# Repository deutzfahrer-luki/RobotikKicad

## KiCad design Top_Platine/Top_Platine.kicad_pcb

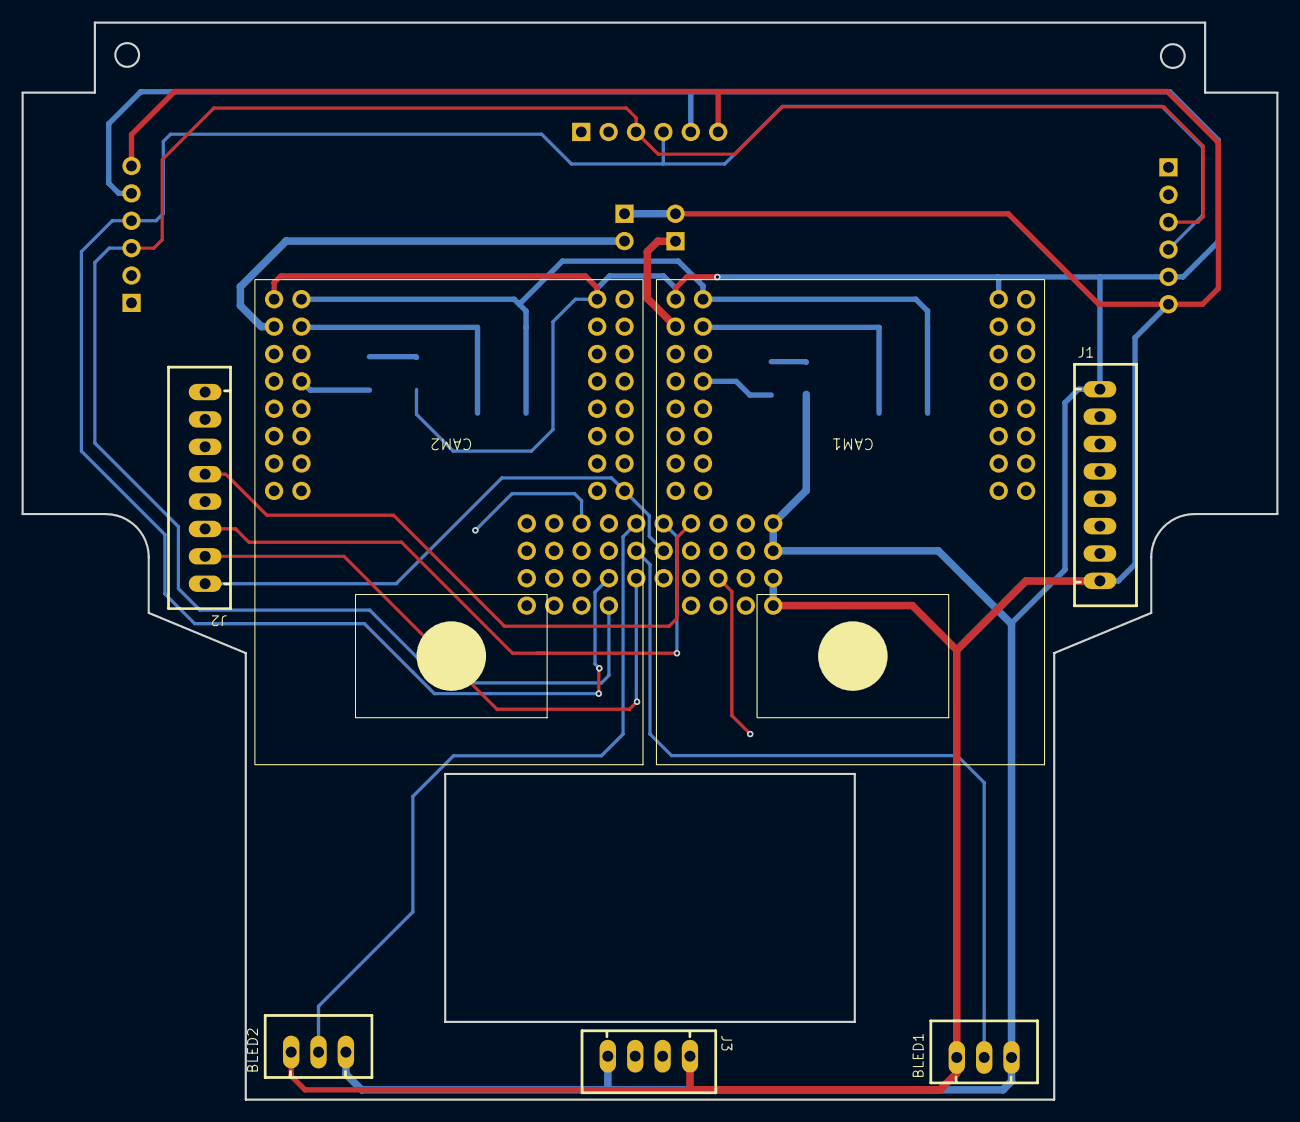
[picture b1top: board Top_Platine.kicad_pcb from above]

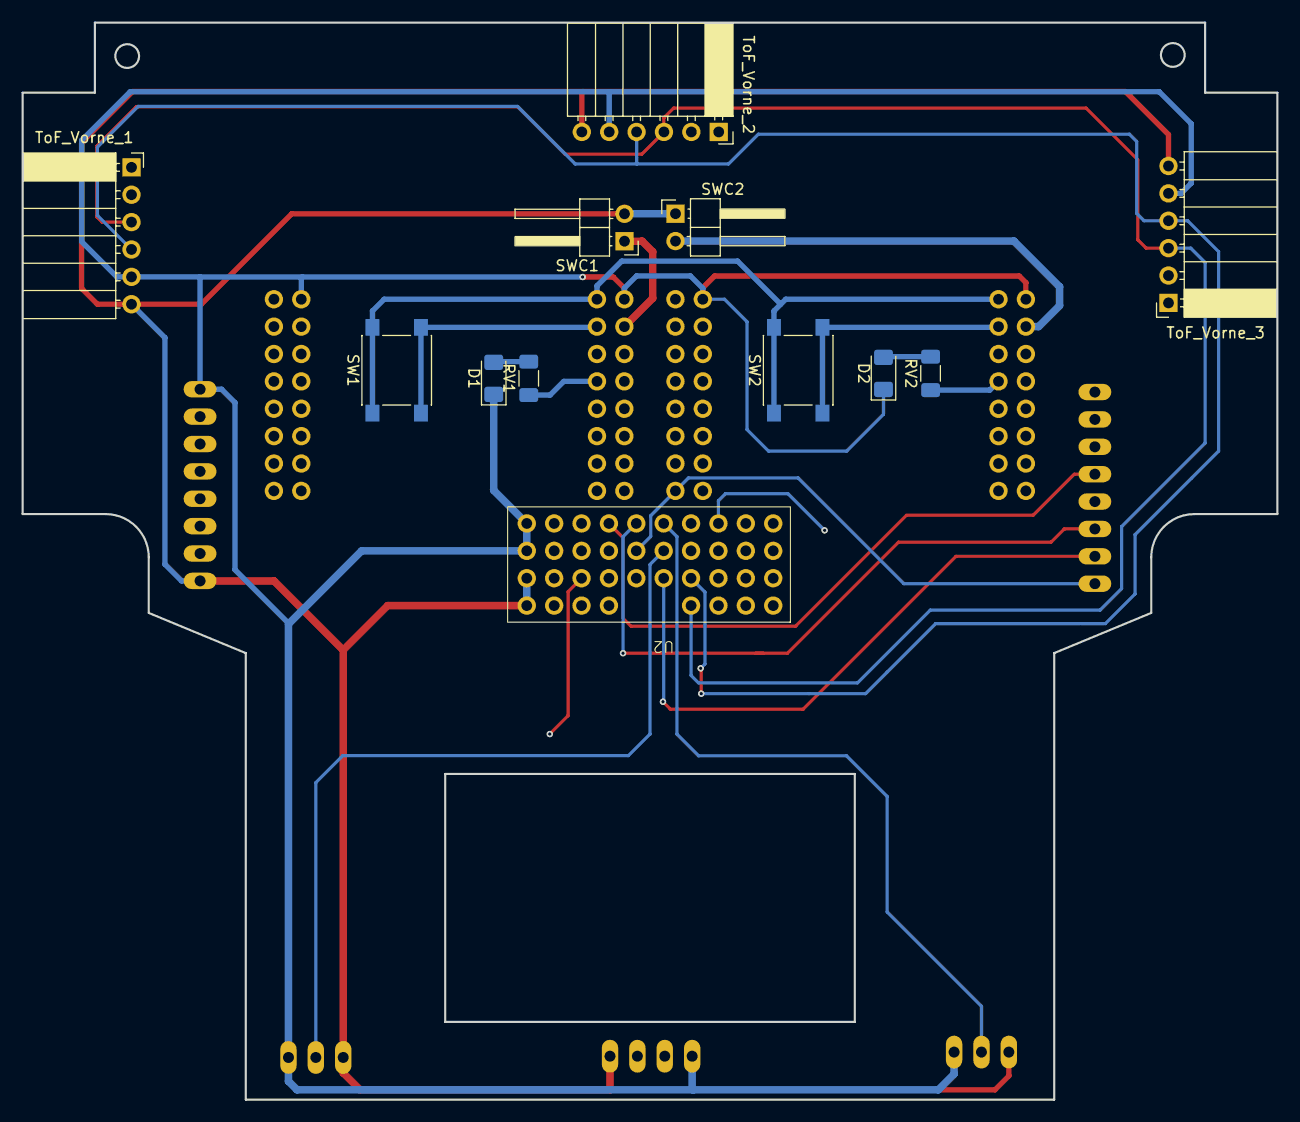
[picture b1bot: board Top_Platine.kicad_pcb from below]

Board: 4 copper layers, 116.4 x 99.9 mm, 19 parts (12 on the bottom side), 42 nets.

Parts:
BLED1, BLED2: Conn_01x03_Pin; JST-XH-03-PACKAGE-LONG-PAD
CAM1, CAM2: OpenMV_RT1062
D1, D2: LED; LED_1206_3216Metric_Pad1.42x1.75mm_HandSolder
J1, J2: Conn_01x08_Pin; JST-XH-08-PACKAGE-LONG-PAD
J3: Conn_01x04_Pin; JST-XH-04-PACKAGE-LONG-PAD
RV1, RV2: 220; R_1206_3216Metric_Pad1.30x1.75mm_HandSolder
SW1, SW2: SW_SPST; SW_SPST_PTS645
SWC1, SWC2: SW_SPST; PinHeader_1x02_P2.54mm_Horizontal
ToF_Vorne_1, ToF_Vorne_2, ToF_Vorne_3: Conn_01x06_Socket; PinSocket_1x06_P2.54mm_Horizontal
U2: Main Conector to Main pcb; Main Conetor

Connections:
+3.3V: CAM1.17 (3.3V), CAM2.17 (3.3V), SW1.1 (A), SW2.1 (A)
+5V: BLED1.1, BLED2.1, J1.8, J3.1, SWC1.2 (B), SWC2.1 (A), ToF_Vorne_1.6, ToF_Vorne_2.6, ToF_Vorne_3.6, U2.5V
/BLED_C1: BLED1.2, U2.LED1 (Beleuchtung_Cam_1)
/BLED_C2: BLED2.2, U2.LED2 (Beleuchtung_Cam_2)
/BUTTON_1: J1.4, U2.UI_B1 (UI_Button_1)
/BUTTON_2: J1.5, U2.UI_B2 (UI_Button_2)
/BUTTON_3: J1.6, U2.UI_B3 (UI_Button_3)
/BUTTON_4: J1.7, U2.UI_B4 (UI_Button_4)
/CS_D: J2.5, U2.CS_D (CS_Display)
/D_D: J2.3, U2.D_D (D_Display)
/INTT_C1: CAM1.29 (P9), U2.R_C1 (Reset_Cam_1)
/INTT_C2: CAM2.29 (P9), U2.R_C2 (Reset_Cam_2)
/INT_C1: CAM1.30 (P10), U2.I_C1 (Interrupt_Cam_1)
/INT_C2: CAM2.30 (P10), U2.I_C2 (Interrupt_Cam_2)
/Kamera/Kamera1/5V: CAM1.26 (VIN), SWC1.1 (A)
/Kamera/Kamera1/State_LED: CAM1.20 (P14), RV1.1
/Kamera/Kamera2/5V: CAM2.26 (VIN), SWC2.2 (B)
/Kamera/Kamera2/State_LED: CAM2.20 (P14), RV2.1
/LED_A: J1.2, U2.LED_A (UI_Led_1)
/LED_B: J1.3, U2.LED_B (UI_Led_2)
/MOSI: J2.1, U2.MOSI
/RES: J2.4, U2.1 (RES_D)
/RE_A: J2.6, U2.RE_A (Encoder_A)
/RE_B: J2.8, U2.RE_B (Encoder_B)
/RE_SW: J2.7, U2.RE_SW (Encoder_Taster)
/RX_C1: CAM1.3 (P5/U_RX/SDA), U2.RX_C1 (RX_Cam_1)
/RX_C2: CAM2.3 (P5/U_RX/SDA), U2.RX_C2 (RX_Cam_2)
/SCK: J2.2, U2.SCK
/SCL: ToF_Vorne_1.3, ToF_Vorne_2.3, ToF_Vorne_3.3, U2.SDA
/SDA: ToF_Vorne_1.4, ToF_Vorne_2.4, ToF_Vorne_3.4, U2.SCL
/TX_C1: CAM1.4 (P4/U_TX/SCL), U2.TX_C1 (TX_Cam_1)
/TX_C2: CAM2.4 (P4/U_TX/SCL), U2.TX_C2 (TX_Cam_2)
/ToF_XS_1: ToF_Vorne_1.1, U2.TXS1 (ToF_XS_1)
/ToF_XS_2: ToF_Vorne_2.1, U2.TXS2 (ToF_XS_2)
/ToF_XS_3: ToF_Vorne_3.1, U2.TXS3 (ToF_XS_3)
GND: BLED1.3, BLED2.3, CAM1.9 (GND), CAM1.25 (GND), CAM2.9 (GND), CAM2.25 (GND), D1.1 (K), D2.1 (K), J1.1, J3.4, ToF_Vorne_1.5, ToF_Vorne_2.5, ToF_Vorne_3.5, U2.GND
unnamed: CAM1.18 (SBL), SW1.2 (B)
unnamed: CAM2.18 (SBL), SW2.2 (B)
unnamed: D1.2 (A), RV1.2
unnamed: D2.2 (A), RV2.2
unnamed: J3.2, U2.D+ (Mega_D+)
unnamed: J3.3, U2.D- (Mega_D-)

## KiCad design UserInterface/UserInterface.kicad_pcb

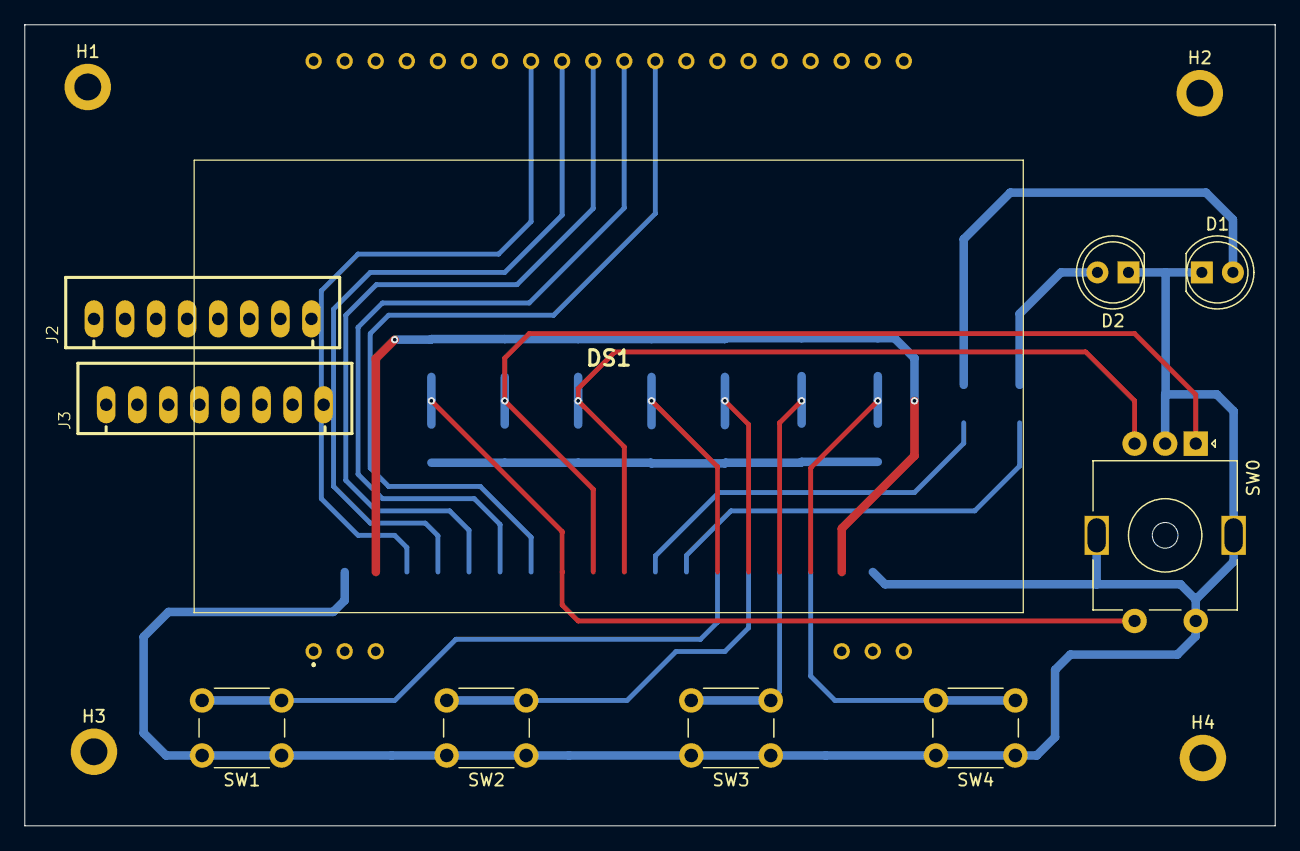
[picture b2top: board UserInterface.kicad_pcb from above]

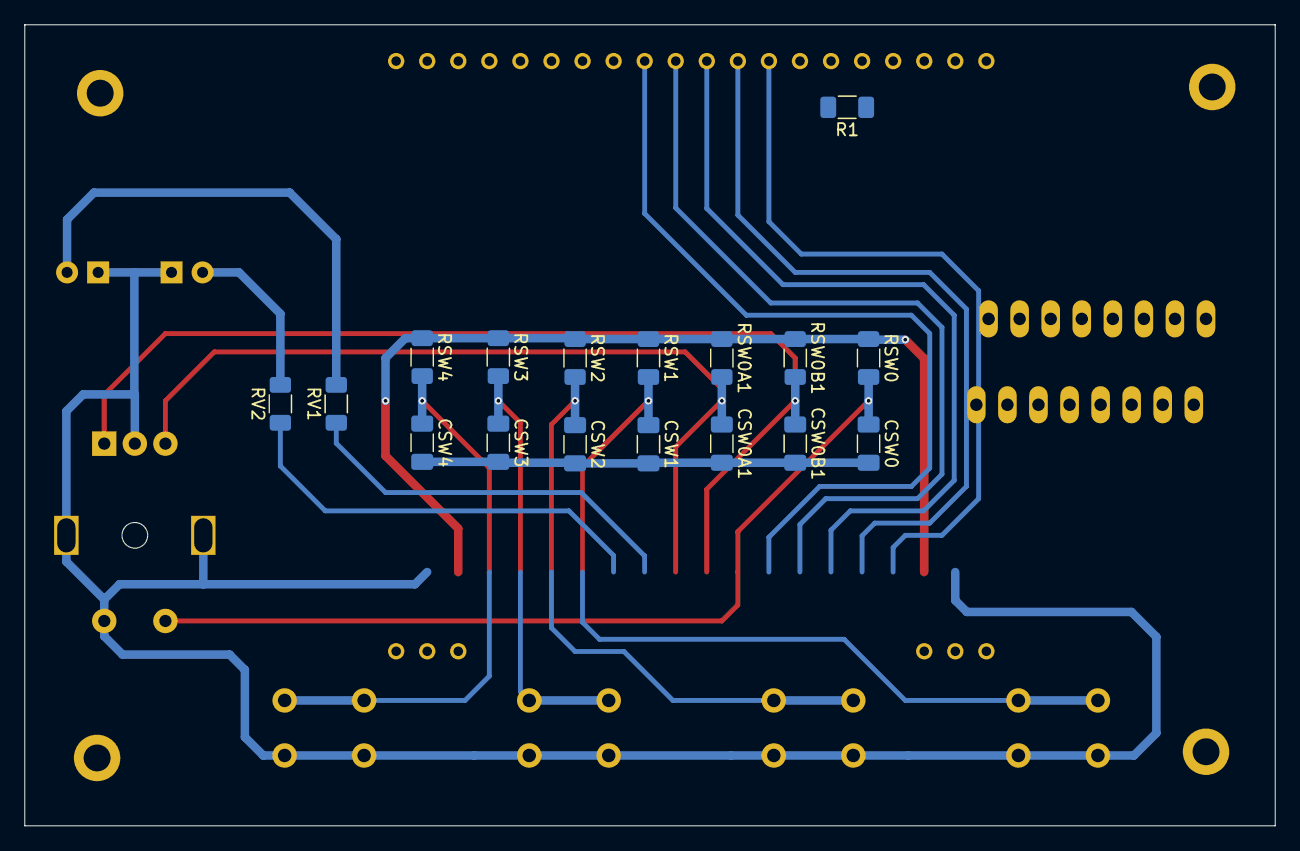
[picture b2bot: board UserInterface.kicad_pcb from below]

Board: 2 copper layers, 102.2 x 65.5 mm, 31 parts (17 on the bottom side), 18 nets.

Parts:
CSW0, CSW0A1, CSW0B1, CSW1, CSW2, CSW3, CSW4: 100n; C_1206_3216Metric_Pad1.33x1.80mm_HandSolder
D1, D2: LED; LED_D5.0mm
DS1: EA_OLEDL128-6GGA; EA OLEDL128-6GGA
H1, H2, H3, H4: MountingHole_Pad; MountingHole_2.2mm_M2_DIN965_Pad
J2, J3: Conn_01x08_Pin; JST-XH-08-PACKAGE-LONG-PAD
R1: 910K; R_1206_3216Metric_Pad1.30x1.75mm_HandSolder
RSW0, RSW0A1, RSW0B1, RSW1, RSW2, RSW3, RSW4: 10k; R_1206_3216Metric_Pad1.30x1.75mm_HandSolder
RV1, RV2: 220R; R_1206_3216Metric_Pad1.30x1.75mm_HandSolder
SW0: RotaryEncoder_Switch_MP; RotaryEncoder_Alps_EC11E-Switch_Vertical_H20mm_MountingHoles
SW1, SW2, SW3, SW4: SW_SPST; SW_PUSH_6mm_H7.3mm

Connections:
+5V: DS1.21 (VCC_1), DS1.22 (VCC_2), DS1.25 (VDD), DS1.39 (VCC_3), DS1.40 (VCC_4), J2.8, RSW0.1, RSW0A1.1, RSW0B1.1, RSW1.1, RSW2.1, RSW3.1, RSW4.1
/BUTTON_1: CSW1.1, J2.4, RSW1.2, SW1.2 (B)
/BUTTON_2: CSW2.1, J2.5, RSW2.2, SW2.2 (B)
/BUTTON_3: CSW3.1, J2.6, RSW3.2, SW3.2 (B)
/BUTTON_4: CSW4.1, J2.7, RSW4.2, SW4.2 (B)
/Display/IREF: DS1.36 (IREF), R1.1
/Display/VCOMH: DS1.37 (VCOMH_1), DS1.38 (VCOMH_2)
/LED_A: J2.2, RV1.1
/LED_B: J2.3, RV2.1
/MOSI: DS1.33 (D1), J3.1
/RES: DS1.30 (RES), J3.4
/RE_A: CSW0B1.1, J3.6, RSW0B1.2, SW0.A
/RE_B: CSW0A1.1, J3.8, RSW0A1.2, SW0.B
/RE_SW: CSW0.1, J3.7, RSW0.2, SW0.S1
/SCK: DS1.32 (D0), J3.2
GND: CSW0.2, CSW0A1.2, CSW0B1.2, CSW1.2, CSW2.2, CSW3.2, CSW4.2, D1.1 (K), D2.1 (K), DS1.23 (GND_1), DS1.24 (GND_2), DS1.26 (BS0), DS1.27 (BS1), DS1.28 (GND_3), DS1.35 (GND_4), H1.1, H2.1, H3.1, H4.1, J2.1, R1.2, SW0.C, SW0.MP, SW0.S2, SW1.1 (A), SW2.1 (A), SW3.1 (A), SW4.1 (A)
unnamed: D1.2 (A), RV1.2
unnamed: D2.2 (A), RV2.2

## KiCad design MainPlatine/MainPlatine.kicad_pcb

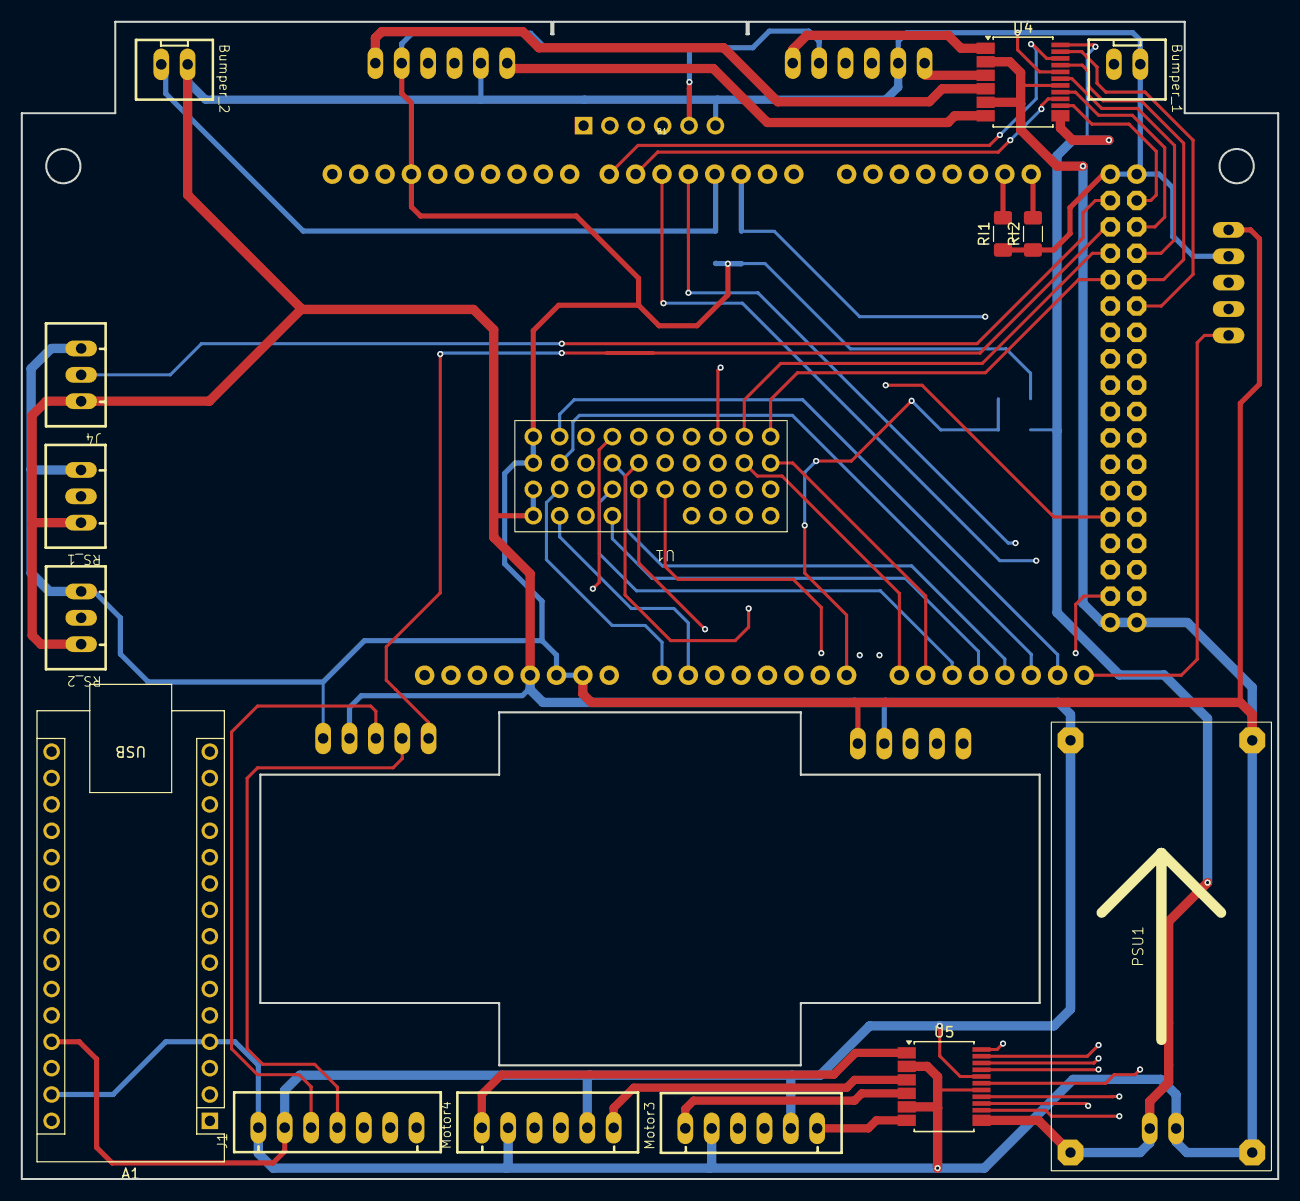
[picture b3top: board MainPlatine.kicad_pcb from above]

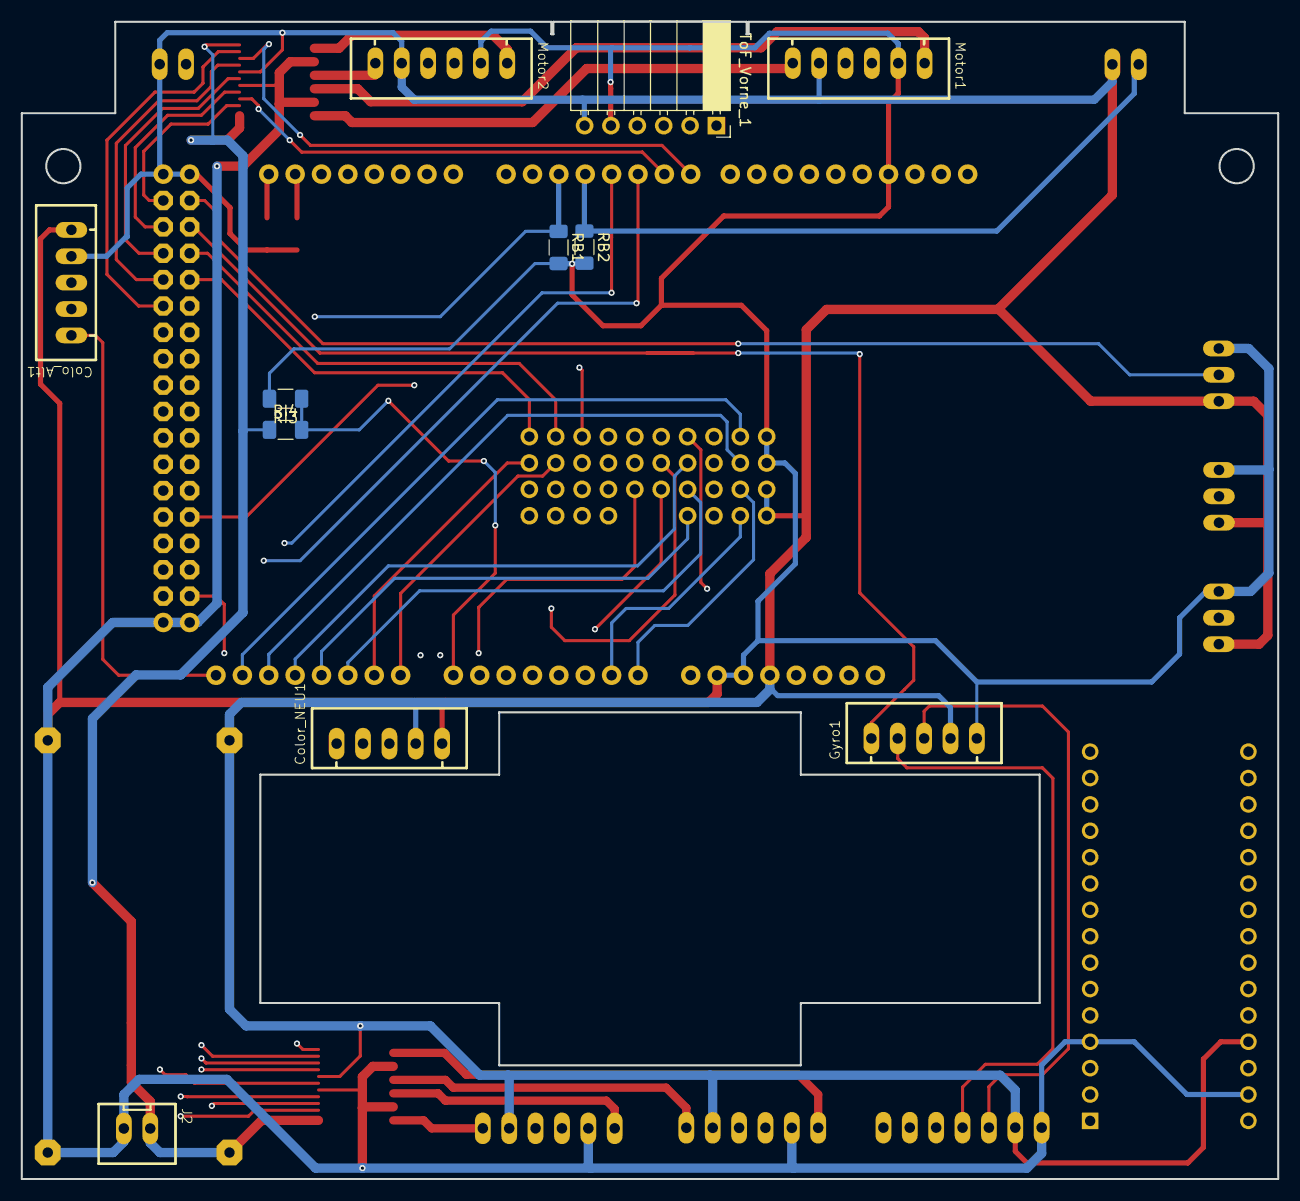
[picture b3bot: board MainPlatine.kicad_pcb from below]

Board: 4 copper layers, 121.0 x 111.5 mm, 27 parts (11 on the bottom side), 74 nets.

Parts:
A1: Arduino_Nano_v2.x; Arduino_Nano
B1: ARDUINO_MEGA_NO_SILK
Bumper_1, Bumper_2: Conn_01x02_Pin; JST-XH-02-PACKAGE-LONG-PAD
Colo_Alt1: Conn_01x05_Pin; JST-XH-05-PACKAGE-LONG-PAD
Color_NEU1: Conn_01x05_Pin; JST-XH-05-PACKAGE-LONG-PAD
Gyro1: Conn_01x05_Pin; JST-XH-05-PACKAGE-LONG-PAD
J1: Conn_01x07_Pin; JST-XH-07-PACKAGE-LONG-PAD
J2: Conn_01x02_Pin; JST-XH-02-PACKAGE-LONG-PAD
J4: Conn_01x03_Pin; JST-XH-03-PACKAGE-LONG-PAD
Motor1, Motor2, Motor3, Motor4: Conn_01x06_Pin; JST-XH-06-PACKAGE-LONG-PAD
PSU1: Untitled_1
RB1, RB2: 10k; R_1206_3216Metric_Pad1.30x1.75mm_HandSolder
RI1, RI2, RI3, RI4: 10k; R_1206_3216Metric_Pad1.30x1.75mm_HandSolder
RS_1, RS_2: Conn_01x03_Pin; JST-XH-03-PACKAGE-LONG-PAD
ToF_Vorne_1: Conn_01x06_Socket; PinSocket_1x06_P2.54mm_Horizontal
U1: Main Conector to Main pcb; Main Conetor
U4, U5: TB6612FNG; SSOP-24_5.3x8.2mm_P0.65mm

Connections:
+5V: A1.27 (+5V), B1.5V, Bumper_1.1, Bumper_2.1, Colo_Alt1.4, Color_NEU1.4, Gyro1.4, J1.2, J4.1, Motor1.5, Motor2.5, Motor3.5, Motor4.5, PSU1.OUT+ (VOUT+), RI1.1, RI2.1, RS_1.1, RS_2.1, ToF_Vorne_1.6, U1.5V, U4.20 (VCC), U5.20 (VCC)
/6V: J2.1, PSU1.IN+ (VIN+), RI4.1, U4.14 (VM3), U4.24 (VM1), U5.14 (VM3), U5.24 (VM1)
/ARD_RX_2: B1.17 (17(RX2)), U1.TX_C2 (TX_Cam_2)
/ARD_RX_3: A1.2 (D0/RX), B1.14 (14(TX3))
/ARD_TX_2: B1.16 (16(TX2)), U1.RX_C2 (RX_Cam_2)
/ARD_TX_3: A1.1 (D1/TX), B1.15 (15(RX3))
/BAT_ADC: B1.A7, RI3.1, RI4.2
/Bumper_Links: B1.2, Bumper_1.2, RB1.1
/Bumper_Rechts: B1.3, Bumper_2.2, RB2.1
/CS_D: B1.53 (53/~CS), U1.CS_D (CS_Display)
/Color_NEW_IO: B1.48, Color_NEU1.1
/Color_Old_Interrupt: B1.A15, Colo_Alt1.1
/D_D: B1.46, U1.D_D (D_Display)
/ENC1_A: A1.12 (D9), Motor2.4
/ENC1_B: A1.11 (D8), Motor2.3
/ENC2_A: A1.10 (D7), Motor1.4
/ENC2_B: A1.9 (D6), Motor1.3
/ENC3_A: A1.6 (D3), Motor4.4
/ENC3_B: A1.5 (D2), Motor4.3
/ENC4_A: A1.8 (D5), Motor3.4
/ENC4_B: A1.7 (D4), Motor3.3
/Encoder_A: B1.A12, U1.RE_A (Encoder_A)
/Encoder_B: B1.A10, U1.RE_B (Encoder_B)
/Encoder_SW: B1.A11, U1.RE_SW (Encoder_Taster)
/GYRO_RST: B1.24, Gyro1.1
/IO_CAM2: B1.26, U1.R_C2 (Reset_Cam_2)
/Interrupt_Cam1: B1.A8, U1.I_C2 (Interrupt_Cam_2)
/LEDB_U: B1.22, J4.2
/LED_C1: B1.40, U1.LED2 (Beleuchtung_Cam_2)
/MISO: B1.50 (50/MISO), U1.MOSI
/MOSI: B1.51 (51/MOSI), U1.MISO
/MOT1_IN1: B1.31, U4.23 (PWMA)
/MOT1_IN2: B1.29, U4.21 (AIN1)
/MOT1_PWM: B1.7, U4.22 (AIN2)
/MOT2_IN1: B1.23, U4.15 (PWMB)
/MOT2_IN2: B1.25, U4.17 (BIN1)
/MOT2_PWM: B1.6, U4.16 (BIN2)
/MOT3_IN1: B1.49, U5.23 (PWMA)
/MOT3_IN2: B1.47, U5.21 (AIN1)
/MOT3_PWM: B1.5, U5.22 (AIN2)
/MOT4_IN1: B1.43, U5.15 (PWMB)
/MOT4_IN2: B1.45, U5.17 (BIN1)
/MOT4_PWM: B1.4, U5.16 (BIN2)
/MOT_STBY: B1.27, U4.19 (STBY), U5.19 (STBY)
/RES_D: B1.8, U1.1 (RES_D)
/RS_Servo_1: B1.10, RS_1.2
/RS_Servo_2: B1.9, RS_2.2
/SCK: B1.52 (52/SCK), U1.SCK
/SCL: B1.21 (21(SCL)), Color_NEU1.3, Gyro1.3, J1.3, RI2.2, ToF_Vorne_1.4, U1.SCL
/SDA: B1.20 (20(SDA)), Color_NEU1.2, Gyro1.2, J1.4, RI1.2, ToF_Vorne_1.3, U1.SDA
/SW_SCL: B1.33, Colo_Alt1.3
/SW_SDA: B1.35, Colo_Alt1.2
/Tof_XS_0: B1.30, ToF_Vorne_1.1
/Tof_XS_1: B1.37, J1.7
/Tof_XS_2: B1.39, J1.6
/Tof_XS_3: B1.41, J1.5
/Tof_XS_4: B1.32, U1.TXS1 (ToF_XS_1)
/Tof_XS_5: B1.34, U1.TXS2 (ToF_XS_2)
/Tof_XS_6: B1.36, U1.TXS3 (ToF_XS_3)
/Treiber1/A+: Motor2.1, U4.1 (AO1)
/Treiber1/A-: Motor2.6, U4.5 (AO2)
/Treiber1/B+: Motor1.1, U4.7 (BO2)
/Treiber1/B-: Motor1.6, U4.11 (BO1)
/Treiber2/A+: Motor4.1, U5.1 (AO1)
/Treiber2/A-: Motor4.6, U5.5 (AO2)
/Treiber2/B+: Motor3.1, U5.7 (BO2)
/Treiber2/B-: Motor3.6, U5.11 (BO1)
/UI_Button_1: B1.A14, U1.UI_B1 (UI_Button_1)
/UI_Button_2: B1.A13, U1.UI_B2 (UI_Button_2)
/UI_Button_3: B1.A0, U1.UI_B3 (UI_Button_3)
/UI_Button_4: B1.A1, U1.UI_B4 (UI_Button_4)
/UI_LED_1: B1.44, U1.LED_A (UI_Led_1)
/UI_LED_2: B1.42, U1.LED_B (UI_Led_2)
GND: A1.4 (GND), A1.29 (GND), B1.GND, Colo_Alt1.5, Color_NEU1.5, Gyro1.5, J1.1, J2.2, J4.3, Motor1.2, Motor2.2, Motor3.2, Motor4.2, PSU1.IN- (VIN-), PSU1.OUT- (VOUT-), RB1.2, RB2.2, RI3.2, RS_1.3, RS_2.3, ToF_Vorne_1.5, U1.GND, U4.3 (PGND1), U4.9 (PGND2), U4.18 (GND), U5.3 (PGND1), U5.9 (PGND2), U5.18 (GND)

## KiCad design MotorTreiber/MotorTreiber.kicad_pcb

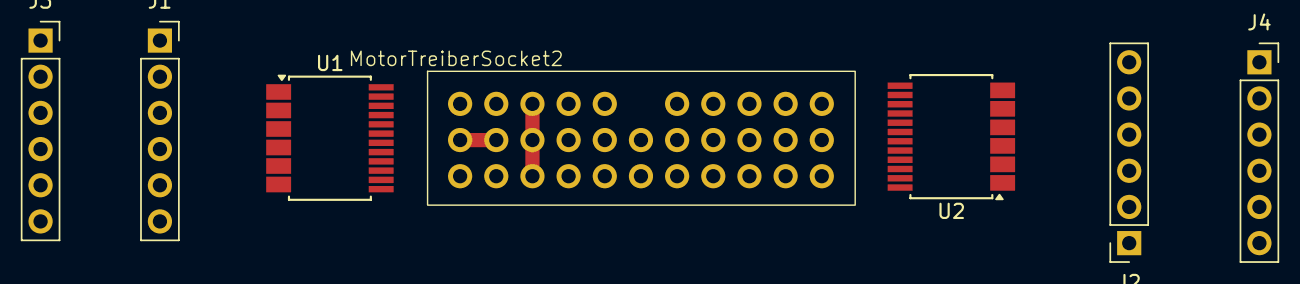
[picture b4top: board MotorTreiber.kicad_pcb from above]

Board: 2 copper layers, 7 parts (0 on the bottom side), 31 nets.

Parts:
J1, J2, J3, J4: Conn_01x06_Pin; PinSocket_1x06_P2.54mm_Vertical
MotorTreiberSocket2: SocketMotor
U1, U2: TB6612FNG; SSOP-24_5.3x8.2mm_P0.65mm

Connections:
+5V: J1.5, J2.5, J3.5, J4.5, U1.20 (VCC), U2.20 (VCC)
/6V: MotorTreiberSocket2.6V (PWR_Motor), U1.13 (VM2), U1.14 (VM3), U1.24 (VM1), U2.13 (VM2), U2.14 (VM3), U2.24 (VM1)
/ENC1_A: J2.4, MotorTreiberSocket2.ENC1_A
/ENC2_A: J4.4, MotorTreiberSocket2.ENC2_A
/ENC2_B: J2.3, J4.3, MotorTreiberSocket2.ENC2_B
/ENC3_A: J1.4, MotorTreiberSocket2.ENC3_A
/ENC3_B: J1.3, MotorTreiberSocket2.ENC3_B
/ENC4_A: J3.4, MotorTreiberSocket2.ENC4_A
/ENC4_B: J3.3, MotorTreiberSocket2.ENC4_B
/MOT1_IN1: MotorTreiberSocket2.MOT1_IN1, U2.23 (PWMA)
/MOT1_IN2: MotorTreiberSocket2.MOT1_IN2, U2.21 (AIN1)
/MOT1_PWM: MotorTreiberSocket2.MOT1_PWM, U2.22 (AIN2)
/MOT2_IN1: MotorTreiberSocket2.MOT2_IN1, U2.15 (PWMB)
/MOT2_IN2: MotorTreiberSocket2.MOT2_IN2, U2.17 (BIN1)
/MOT2_PWM: MotorTreiberSocket2.MOT2_PWM, U2.16 (BIN2)
/MOT3_IN1: MotorTreiberSocket2.MOT3_IN1, U1.23 (PWMA)
/MOT3_IN2: MotorTreiberSocket2.MOT3_IN2, U1.21 (AIN1)
/MOT3_PWM: MotorTreiberSocket2.MOT3_PWM, U1.22 (AIN2)
/MOT4_IN1: MotorTreiberSocket2.MOT4_IN1, U1.15 (PWMB)
/MOT4_IN2: MotorTreiberSocket2.MOT4_IN2, U1.17 (BIN1)
/MOT4_PWM: MotorTreiberSocket2.MOT4_PWM, U1.16 (BIN2)
/MOT_STBY: MotorTreiberSocket2.MOT_STBY, U1.19 (STBY), U2.19 (STBY)
/Treiber1/A+: J1.1, U1.1 (AO1)
/Treiber1/A-: J1.6, U1.5 (AO2)
/Treiber1/B+: J3.1, U1.11 (BO1)
/Treiber1/B-: J3.6, U1.7 (BO2)
/Treiber2/A+: J2.1, U2.1 (AO1)
/Treiber2/A-: J2.6, U2.5 (AO2)
/Treiber2/B+: J4.1, U2.11 (BO1)
/Treiber2/B-: J4.6, U2.7 (BO2)
GND: J1.2, J2.2, J3.2, J4.2, U1.3 (PGND1), U1.9 (PGND2), U1.18 (GND), U2.3 (PGND1), U2.9 (PGND2), U2.18 (GND)

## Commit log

2025-05-01 shittiy
2025-05-09 add new
2025-05-10 add main PCB
2025-05-10 add pdf main sch
2025-05-10 fix main pcb
2025-05-10 update new
2025-05-10 ready to fix ui pcb
2025-05-10 read by lk
2025-05-20 add idk
2025-05-21 add step ui
2025-05-21 add step top
